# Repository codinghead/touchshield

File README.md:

QTouchShield for Arduino
========================

Introduction to the project
---------------------------

The QTouchShield for Arduino project aims to design a hardware platform for the Arduino MEGA that supports up to 32 configurable capacitive touch inputs.

The inputs can be configured as:

* Buttons
* Sliders
* Wheels
* Proximity sensors

Additionally the project includes the necessary firmware required by the shield's microcontroller to enable this functionality.

Key Capabilties
---------------
* Support up to 32 capacitive touch inputs supporting:
	* up to 8 sliders/wheels
	* up to 32 buttons
	* up to 32 proximity sensors
* Configuration via SPI or UART (RX/TX) interfaces
* Arduino library to simplify integration into sketches

Licensing
---------

The hardware is licensed under the Creative Commons ShareAlike license:

> This work is licensed under the Creative Commons Attribution-ShareAlike 3.0 Unported License.
> To view a copy of this license, visit [http://creativecommons.org/licenses/by-sa/3.0/] (http://creativecommons.org/licenses/by-sa/3.0/) or send
> a letter to:
> Creative Commons, 444 Castro Street, Suite 900, Mountain View, California, 94041, USA.

The software for the project is yet to be developed.

Project Page
------------

For all current information, visit the project page at [codinghead.github.com/touchshield] (http://codinghead.github.com/touchshield/).

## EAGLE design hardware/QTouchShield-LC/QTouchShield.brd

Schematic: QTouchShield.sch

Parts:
C1: 10uF/35V; PANASONIC_C
C33, C40, C43, C45, C47, C49, C51: 100nF; 0805
C34, C41, C44, C46, C48, C50, C52: 33nF; 0805
C35, C38: 2.2uF; 1210
C36, C37: 470pF; 0805
C39, C42: 4.7uF; 1210
IC1: AT32UC3C0512CJEDEC-MS-026; LQFP144
J1: SENSOR 00...07; 2X8-V-MALE-SMT-HARWIN
J2: SENSOR 08...15; 2X8-V-MALE-SMT-HARWIN
J3: SENSOR 16...23; 2X8-V-MALE-SMT-HARWIN
J4: SENSOR 24...31; 2X8-V-MALE-SMT-HARWIN
J5: RES 00...07; 2X8-V-FEMALE-SMT-HARWIN
J6: RES 08...15; 2X8-V-FEMALE-SMT-HARWIN
J7: RES 16...23; 2X8-V-FEMALE-SMT-HARWIN
J8: RES 24...31; 2X8-V-FEMALE-SMT-HARWIN
J9: CAP 00...07; 2X8-V-FEMALE-SMT-HARWIN
J10: CAP 08...15; 2X8-V-FEMALE-SMT-HARWIN
J11: CAP 16...23; 2X8-V-FEMALE-SMT-HARWIN
J12: CAP 24...31; 2X8-V-FEMALE-SMT-HARWIN
J13: SPI-MEGA; 2X4-V-MALE-SMT-HARWIN
J14: SPI-UNO; 2X4-V-MALE-SMT-HARWIN
J15: COMMS Select; 2X8-V-MALE-SMT-HARWIN
J16: DETECT00...15; 2X8-V-MALE-SMT-HARWIN
J17: DETECT16...31; 2X8-V-MALE-SMT-HARWIN
J18: JTAG; 2X5-V-MALE-SMT-HARWIN
J19: TOUCH DATA; 2X5-V-MALE-SMT-HARWIN
JP1: COMMS_SELECT; 1X03
LED1: Yellow; LED-1206
LED2: Green; LED-1206
Q1, Q2, Q3, Q4, Q5, Q6: BSS138; SOT23-3
R1, R2: 39R; 0805
R33, R34: 470Ohm; 0805
R35: 10K; 0805
S1: RESET; TACTILE_SWITCH_SMD
SJ5: RESET-LINK; SJ
U1: ARDUINO-2560-MEGA-R3-SMD; ARDUINO-2560-R3-SMD
X1: Firmware Upgrade Port; PN87520

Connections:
ADCVREFN: C51.1, C52.1, IC1.35 (ADCVREFN)
ADCVREFP: C51.2, C52.2, IC1.34 (ADCVREFP)
ADT-SPI0-MISO: J13.2, J14.2, Q3.2 (S)
ADT-SPI0-MOSI: J13.4, J14.4, Q4.2 (S)
ADT-SPI0-SCK: J13.6, J14.6, Q2.2 (S)
ADT-SPI0-SS: J13.8, J14.8, Q1.2 (S)
ADT-USART0-RXD: J15.4, J15.8, J15.12, J15.16, Q5.2 (S)
ADT-USART0-TXD: J15.2, J15.6, J15.10, J15.14, Q6.2 (S)
ARDUINO_RESET: SJ5.1, U1.RESET
GND: C1.-, C33.2, C34.2, C35.2, C36.2, C37.2, C38.2, C39.2, C40.2, C41.2, C42.2, C43.2, C44.2, C45.2, C46.2, C47.2, C48.2, C49.2, C50.2, IC1.6 (GNDIO1), IC1.37 (GNDANA), IC1.52 (GNDPLL), IC1.56 (GNDCORE), IC1.76 (GNDIO2), IC1.104 (GNDIO3-1), IC1.119 (GNDIO3-2), J1.2, J1.4, J1.6, J1.8, J1.10, J1.12, J1.14, J1.16, J2.2, J2.4, J2.6, J2.8, J2.10, J2.12, J2.14, J2.16, J3.2, J3.4, J3.6, J3.8, J3.10, J3.12, J3.14, J3.16, J4.2, J4.4, J4.6, J4.8, J4.10, J4.12, J4.14, J4.16, J18.2, J18.10, J19.9, JP1.3, LED1.C, LED2.C, S1.1, S1.2, U1.GND_1, U1.GND_2, X1.4
IOREF: Q1.1 (G), Q2.1 (G), Q3.1 (G), Q4.1 (G), Q5.1 (G), Q6.1 (G), U1.IOREF
JTAG_RESET: IC1.142 (RESET_N), J18.6, R35.2, S1.3, S1.4, SJ5.2
JTAG_TCK: IC1.1 (PA00), J18.1
JTAG_TDI: IC1.2 (PA01), J18.9
JTAG_TDO: IC1.3 (PA02), J18.3
JTAG_TMS: IC1.4 (PA03), J18.5
MISO-MEGA: J13.1, U1.50
MOSI-MEGA: J13.3, U1.51
unnamed: LED1.A, R33.1
unnamed: J4.15, J8.16
unnamed: J4.13, J8.14
unnamed: J4.11, J8.12
unnamed: J4.9, J8.10
unnamed: J4.7, J8.8
unnamed: J4.5, J8.6
unnamed: J4.3, J8.4
unnamed: J4.1, J8.2
unnamed: J3.15, J7.16
unnamed: J3.13, J7.14
unnamed: J3.11, J7.12
unnamed: J3.9, J7.10
unnamed: J3.7, J7.8
unnamed: J3.5, J7.6
unnamed: J3.3, J7.4
unnamed: J3.1, J7.2
unnamed: J2.15, J6.16
unnamed: J2.13, J6.14
unnamed: J2.11, J6.12
unnamed: J2.9, J6.10
unnamed: J2.7, J6.8
unnamed: J2.5, J6.6
unnamed: J2.3, J6.4
unnamed: J2.1, J6.2
unnamed: J1.15, J5.16
unnamed: J1.13, J5.14
unnamed: J1.11, J5.12
unnamed: J1.9, J5.10
unnamed: J1.7, J5.8
unnamed: J1.5, J5.6
unnamed: J1.3, J5.4
unnamed: J1.1, J5.2
unnamed: R1.2, X1.2
unnamed: R2.2, X1.3
unnamed: LED2.A, R34.1
QT-DETECT-GENERAL: IC1.21 (PA04), R33.2
RX0: J15.3, U1.RX_PWM00 (0(RX0))
RX1: J15.15, U1.RX1_19 (19(RX1))
RX2: J15.11, U1.RX2_17 (17(RX2))
RX3: J15.7, U1.RX3_15 (15(RX3))
SCK-MEGA: J13.5, U1.52
SDT-SPI0-MISO: IC1.112 (PD05), Q3.3 (D)
SDT-SPI0-MOSI: IC1.111 (PD04), Q4.3 (D)
SDT-SPI0-SCK: IC1.113 (PD06), Q2.3 (D)
SDT-SPI0-SS: IC1.110 (PD03), Q1.3 (D)
SDT-USART0-RXD: IC1.108 (PD01), Q6.3 (D)
SDT-USART0-TXD: IC1.107 (PD00), Q5.3 (D)
SHIELD-DATA-TRANSFER-COM-SELECT: IC1.109 (PD02), JP1.2
SHIELD-DATA-TRANSFER-VISUAL-OUTPUT: IC1.22 (PA05), R34.2
SHIELD-DETECT0: IC1.23 (PA06), J16.1
SHIELD-DETECT1: IC1.24 (PA07), J16.2
SHIELD-DETECT2: IC1.25 (PA08), J16.3
SHIELD-DETECT3: IC1.26 (PA09), J16.4
SHIELD-DETECT4: IC1.27 (PA10), J16.5
SHIELD-DETECT5: IC1.28 (PA11), J16.6
SHIELD-DETECT6: IC1.29 (PA12), J16.7
SHIELD-DETECT7: IC1.30 (PA13), J16.8
SHIELD-DETECT8: IC1.31 (PA14), J16.9
SHIELD-DETECT9: IC1.32 (PA15), J16.10
SHIELD-DETECT10: IC1.33 (PA16), J16.11
SHIELD-DETECT11: IC1.36 (PA19), J16.12
SHIELD-DETECT12: IC1.39 (PA20), J16.13
SHIELD-DETECT13: IC1.40 (PA21), J16.14
SHIELD-DETECT14: IC1.41 (PA22), J16.15
SHIELD-DETECT15: IC1.42 (PA23), J16.16
SHIELD-DETECT16: IC1.43 (PA24), J17.15
SHIELD-DETECT17: IC1.44 (PA25), J17.16
SHIELD-DETECT18: IC1.45 (PA26), J17.13
SHIELD-DETECT19: IC1.46 (PA27), J17.14
SHIELD-DETECT20: IC1.47 (PA28), J17.11
SHIELD-DETECT21: IC1.48 (PA29), J17.12
SHIELD-DETECT22: IC1.120 (PD11), J17.9
SHIELD-DETECT23: IC1.121 (PD12), J17.10
SHIELD-DETECT24: IC1.122 (PD13), J17.7
SHIELD-DETECT25: IC1.123 (PD14), J17.8
SHIELD-DETECT26: IC1.124 (PD15), J17.5
SHIELD-DETECT27: IC1.125 (PD16), J17.6
SHIELD-DETECT28: IC1.126 (PD17), J17.3
SHIELD-DETECT29: IC1.127 (PD18), J17.4
SHIELD-DETECT30: IC1.128 (PD19), J17.1
SHIELD-DETECT31: IC1.129 (PD20), J17.2
SNS0: IC1.140 (PB00), J9.1
SNS1: IC1.141 (PB01), J9.3
SNS2: IC1.143 (PB02), J9.5
SNS3: IC1.144 (PB03), J9.7
SNS4: IC1.7 (PB04), J9.9
SNS5: IC1.8 (PB05), J9.11
SNS6: IC1.9 (PB06), J9.13
SNS7: IC1.10 (PB07), J9.15
SNS8: IC1.11 (PB08), J10.1
SNS9: IC1.12 (PB09), J10.3
SNS10: IC1.13 (PB10), J10.5
SNS11: IC1.14 (PB11), J10.7
SNS12: IC1.15 (PB12), J10.9
SNS13: IC1.16 (PB13), J10.11
SNS14: IC1.17 (PB14), J10.13
SNS15: IC1.18 (PB15), J10.15
SNS16: IC1.19 (PB16), J11.1
SNS17: IC1.20 (PB17), J11.3
SNS18: IC1.57 (PB18), J11.5
SNS19: IC1.58 (PB19), J11.7
SNS20: IC1.59 (PB20), J11.9
SNS21: IC1.60 (PB21), J11.11
SNS22: IC1.61 (PB22), J11.13
SNS23: IC1.62 (PB23), J11.15
SNS24: IC1.63 (PB24), J12.1
SNS25: IC1.64 (PB25), J12.3
SNS26: IC1.65 (PB26), J12.5
SNS27: IC1.66 (PB27), J12.7
SNS28: IC1.67 (PB28), J12.9
SNS29: IC1.68 (PB29), J12.11
SNS30: IC1.69 (PB30), J12.13
SNS31: IC1.70 (PB31), J12.15
SNSK0: IC1.71 (PC00), J5.1, J9.2
SNSK1: IC1.72 (PC01), J5.3, J9.4
SNSK2: IC1.73 (PC02), J5.5, J9.6
SNSK3: IC1.74 (PC03), J5.7, J9.8
SNSK4: IC1.77 (PC04), J5.9, J9.10
SNSK5: IC1.78 (PC05), J5.11, J9.12
SNSK6: IC1.79 (PC06), J5.13, J9.14
SNSK7: IC1.80 (PC07), J5.15, J9.16
SNSK8: IC1.81 (PC08), J6.1, J10.2
SNSK9: IC1.82 (PC09), J6.3, J10.4
SNSK10: IC1.83 (PC10), J6.5, J10.6
SNSK11: IC1.84 (PC11), J6.7, J10.8
SNSK12: IC1.85 (PC12), J6.9, J10.10
SNSK13: IC1.86 (PC13), J6.11, J10.12
SNSK14: IC1.87 (PC14), J6.13, J10.14
SNSK15: IC1.88 (PC15), J6.15, J10.16
SNSK16: IC1.89 (PC16), J7.1, J11.2
SNSK17: IC1.90 (PC17), J7.3, J11.4
SNSK18: IC1.91 (PC18), J7.5, J11.6
SNSK19: IC1.92 (PC19), J7.7, J11.8
SNSK20: IC1.93 (PC20), J7.9, J11.10
SNSK21: IC1.94 (PC21), J7.11, J11.12
SNSK22: IC1.95 (PC22), J7.13, J11.14
SNSK23: IC1.96 (PC23), J7.15, J11.16
SNSK24: IC1.97 (PC24), J8.1, J12.2
SNSK25: IC1.98 (PC25), J8.3, J12.4
SNSK26: IC1.99 (PC26), J8.5, J12.6
SNSK27: IC1.100 (PC27), J8.7, J12.8
SNSK28: IC1.101 (PC28), J8.9, J12.10
SNSK29: IC1.102 (PC29), J8.11, J12.12
SNSK30: IC1.105 (PC30), J8.13, J12.14
SNSK31: IC1.106 (PC31), J8.15, J12.16
SPI-MISO-ALT: J14.1, U1.PWM12 (12)
SPI-MOSI-ALT: J14.3, U1.PWM11 (11)
SPI-SCK-ALT: J14.5, U1.PWM13 (13)
SPI-SS-ALT: J14.7, U1.PWM10 (10)
SS-MEGA: J13.7, U1.53
TOUCH_DATA-MISO: IC1.133 (PD24), J19.7
TOUCH_DATA-MOSI: IC1.132 (PD23), J19.6
TOUCH_DATA-SCK: IC1.131 (PD22), J19.8
TOUCH_DATA-SS: IC1.130 (PD21), J19.5
TX0: J15.1, U1.TX_PWM01 (1(TX0))
TX1: J15.13, U1.TX1_18 (18(TX1))
TX2: J15.9, U1.TX2_16 (16(TX2))
TX3: J15.5, U1.TX3_14 (14(TX3))
USB-DM: IC1.50 (DM), R1.1
USB-DP: IC1.51 (DP), R2.1
VCC: C1.+, C33.1, C34.1, C39.1, C40.1, C41.1, C42.1, C43.1, C44.1, C45.1, C46.1, C47.1, C48.1, C49.1, C50.1, IC1.5 (VDDIO1), IC1.38 (VDDANA), IC1.53 (VDDIN_5), IC1.75 (VDDIO2), IC1.103 (VDDIO3-1), IC1.118 (VDDIO3-2), J18.4, J19.10, JP1.1, R35.1, U1.5V_1, X1.1
VDDCORE: C37.1, C38.1, IC1.55 (VDDCORE)
VDDIN_33: C35.1, C36.1, IC1.54 (VDDIN_33)

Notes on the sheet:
SNSK Lines
JTAG
SNS Lines
Detect Output Bus
SHIELD-DATA-TRANSFER
UART-COMS
Mount close to pins 55 & 56
Keep close to pin 5
Keep close to pin 75
Keep close to pin 103
Keep close to
pin 118
Keep close to pin 53
Keep close to pins 34 & 35
Sensor Headers
Detection
Use jumper pair to
select alternative
UART interface
Select between
SPI and UART
Date: 1st August 2012
Revision: 0.1
Author: Stuart Cording
aka /*CODINGHEAD*/
Designed for use with the
Arduino[TM] MEGA 2560 r3
Project: QTouchShield-LC
Keep close to pins 37 & 38
Decoupling capacitors
Supply decoupling capacitors
R35 not mounted
(Only req. when
Arduino is *not*
Use to link AT32UC3C
RESET_N to
Arduino RESET
Mountain View, California, 94041, USA.
Creative Commons, 444 Castro Street, Suite 900,
http://creativecommons.org/licenses/by-sa/3.0/ or send a letter to:

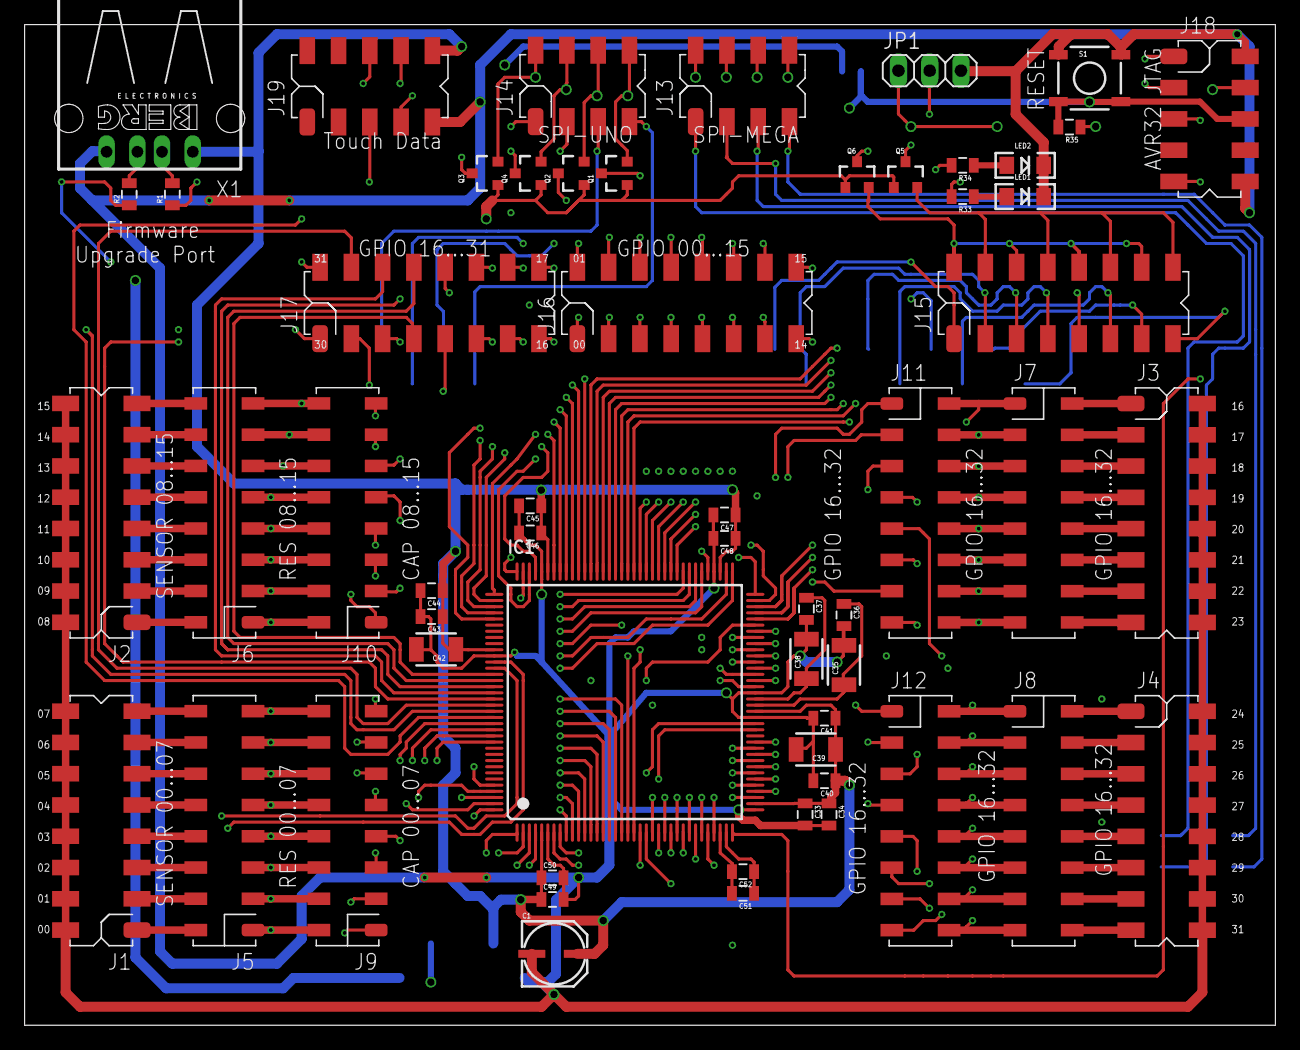
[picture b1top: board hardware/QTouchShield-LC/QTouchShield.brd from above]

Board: 4 copper layers, 101.6 x 81.3 mm, 59 parts (1 on the bottom side), 182 nets.

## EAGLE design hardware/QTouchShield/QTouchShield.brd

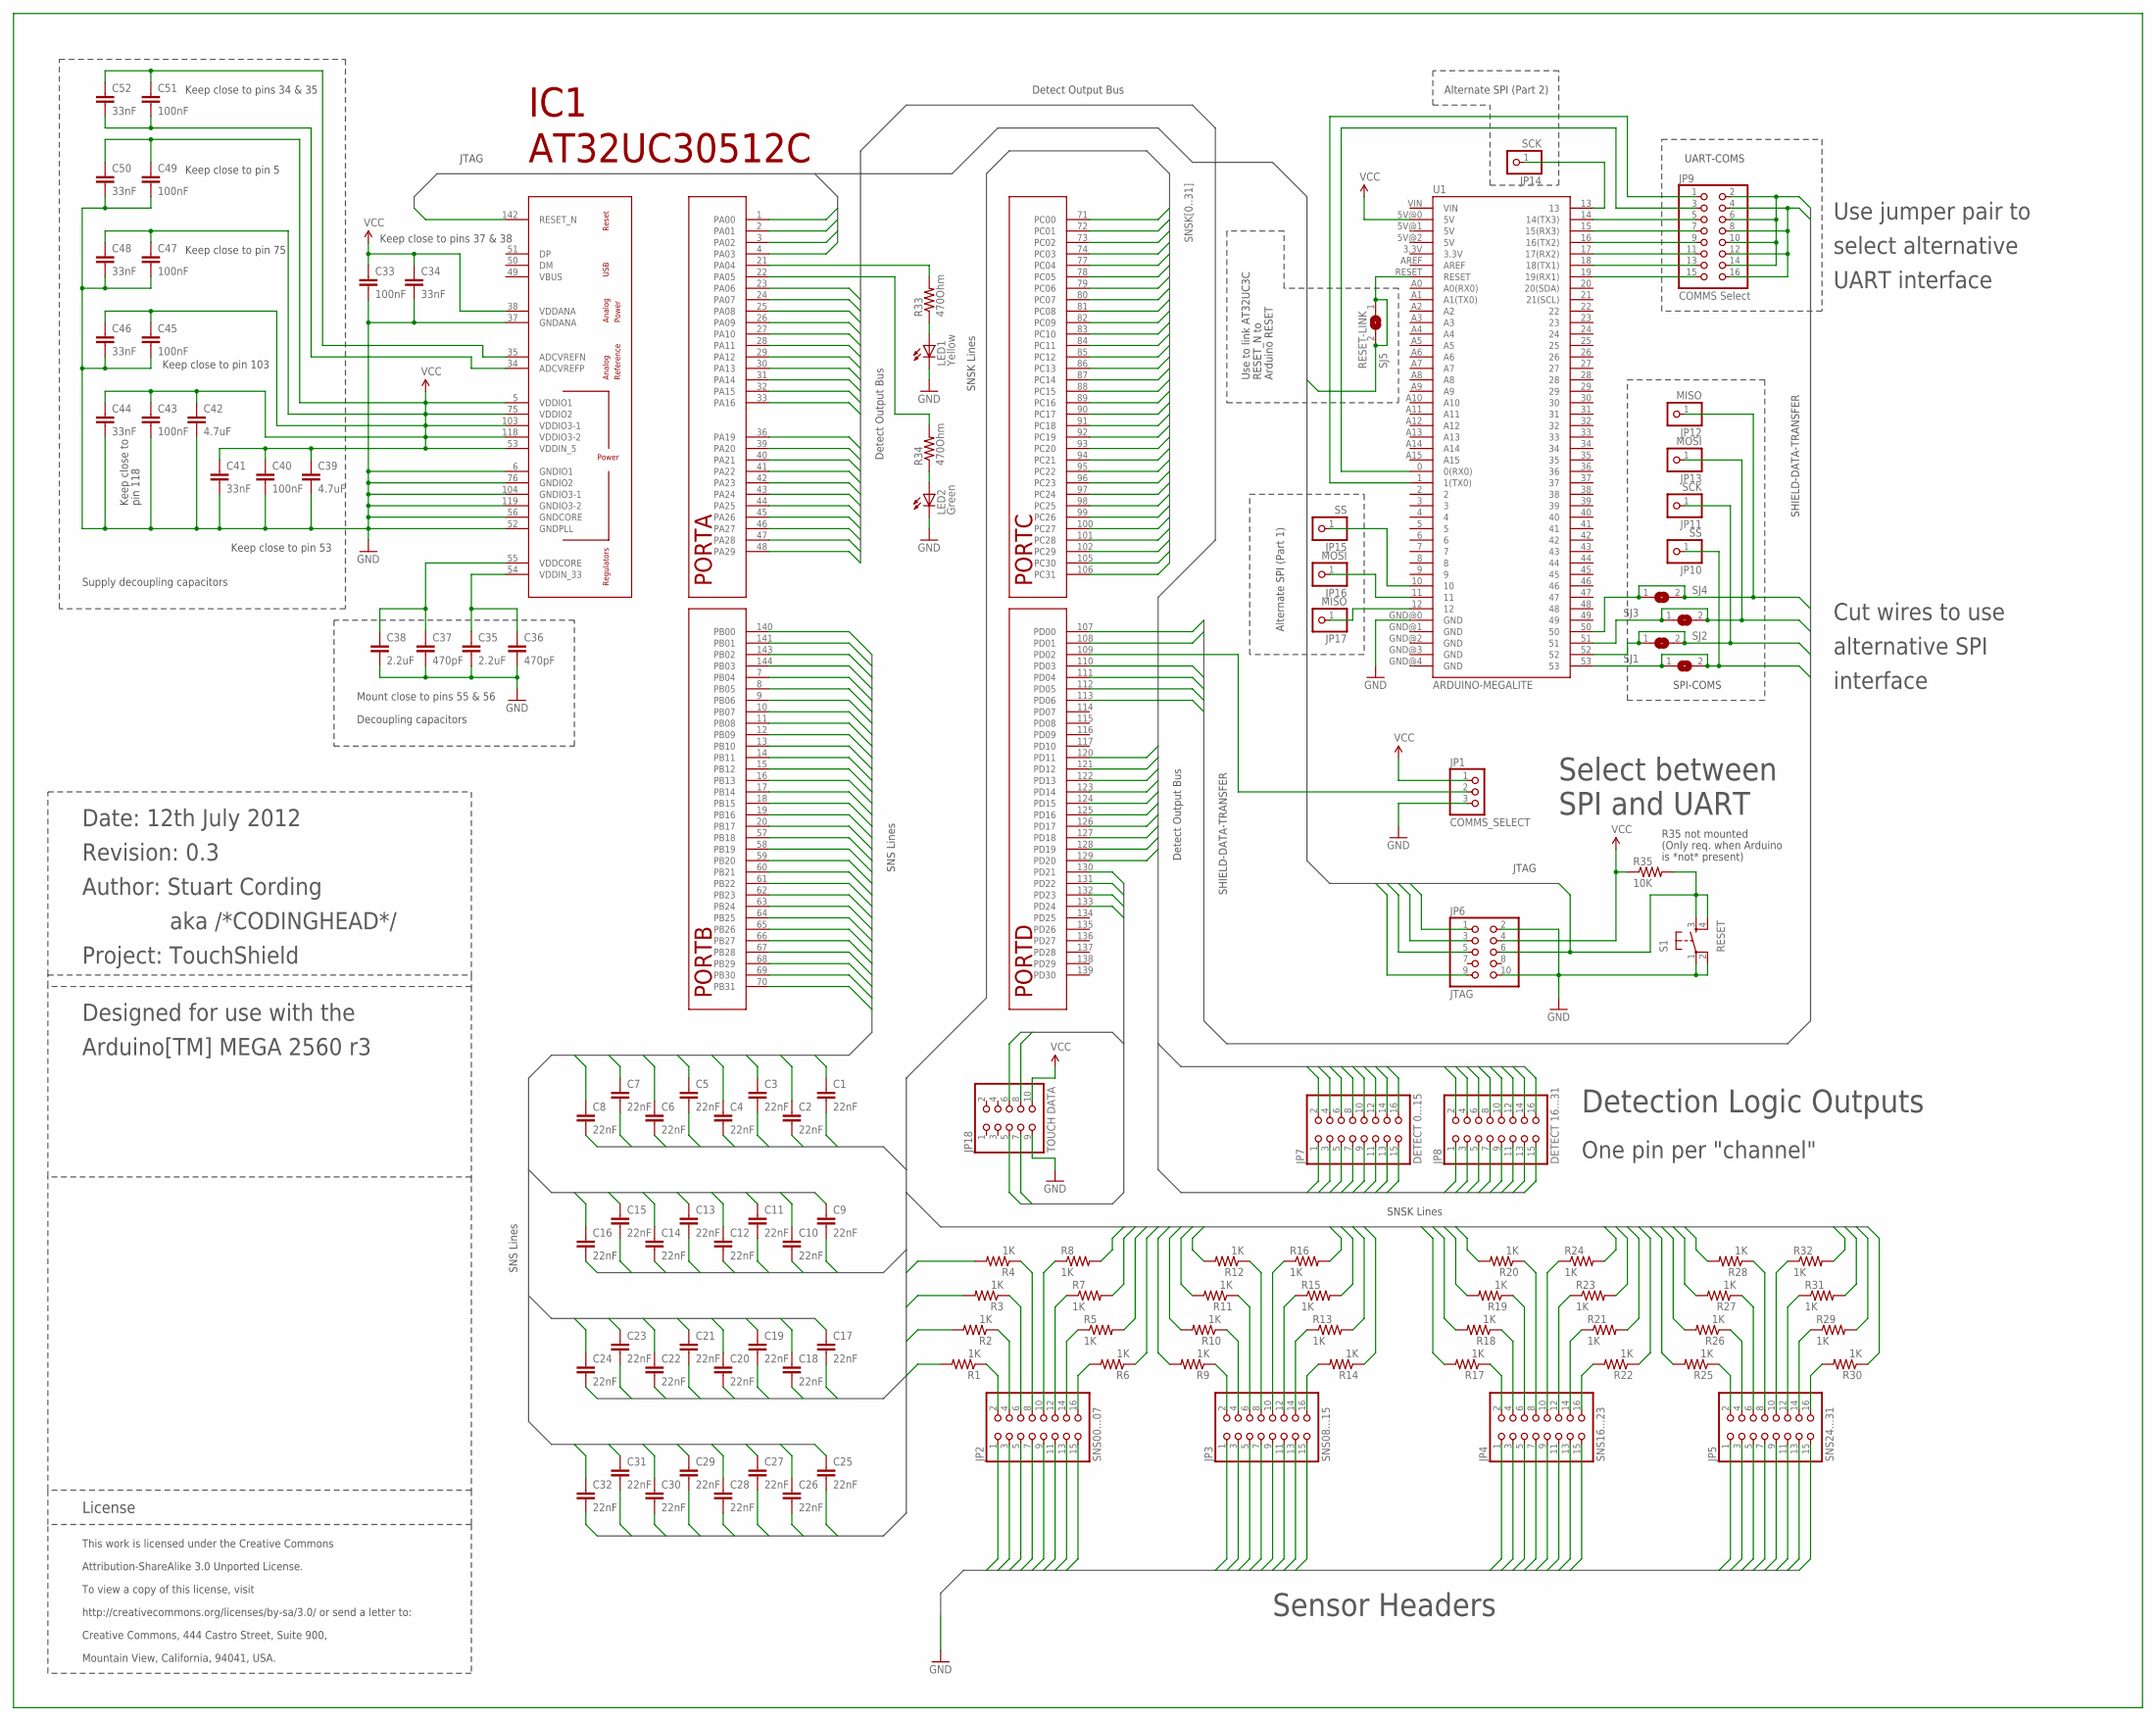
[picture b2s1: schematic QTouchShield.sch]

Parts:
C1, C2, C3, C4, C5, C6, C7, C8, C9, C10, C11, C12, C13, C14, C15, C16, C17, C18, C19, C20, C21, C22, C23, C24, C25, C26, C27, C28, C29, C30, C31, C32: 22nF; 0805
C33, C40, C43, C45, C47, C49, C51: 100nF; 0805
C34, C41, C44, C46, C48, C50, C52: 33nF; 0805
C35, C38: 2.2uF; 1210
C36, C37: 470pF; 0805
C39, C42: 4.7uF; 1210
IC1: AT32UC3C0512CJEDEC-MS-026; LQFP144
JP1: COMMS_SELECT; 1X03
JP2: SNS00...07; 2X08
JP3: SNS08...15; 2X08
JP4: SNS16...23; 2X08
JP5: SNS24...31; 2X08
JP6: JTAG; 2X05
JP7: DETECT 0...15; 2X08
JP8: DETECT 16...31; 2X08
JP9: COMMS Select; 2X08
JP10, JP15: SS; 1X01
JP11, JP14: SCK; 1X01
JP12, JP17: MISO; 1X01
JP13, JP16: MOSI; 1X01
JP18: TOUCH DATA; 2X05
LED1: Yellow; LED-1206
LED2: Green; LED-1206
R1, R2, R3, R4, R5, R6, R7, R8, R9, R10, R11, R12, R13, R14, R15, R16, R17, R18, R19, R20, R21, R22, R23, R24, R25, R26, R27, R28, R29, R30, R31, R32: 1K; 0805
R33, R34: 470Ohm; 0805
R35: 10K; 0805
S1: RESET; TACTILE_SWITCH_SMD
SJ1, SJ2, SJ3, SJ4: SJ
SJ5: RESET-LINK; SJ
U1: ARDUINO-MEGALITE; ARDUINO_MEGA_LITE

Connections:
ADCVREFN: C51.1, C52.1, IC1.35 (ADCVREFN)
ADCVREFP: C51.2, C52.2, IC1.34 (ADCVREFP)
GND: C33.2, C34.2, C35.2, C36.2, C37.2, C38.2, C39.2, C40.2, C41.2, C42.2, C43.2, C44.2, C45.2, C46.2, C47.2, C48.2, C49.2, C50.2, IC1.6 (GNDIO1), IC1.37 (GNDANA), IC1.52 (GNDPLL), IC1.56 (GNDCORE), IC1.76 (GNDIO2), IC1.104 (GNDIO3-1), IC1.119 (GNDIO3-2), JP1.3, JP2.1, JP2.3, JP2.5, JP2.7, JP2.9, JP2.11, JP2.13, JP2.15, JP3.1, JP3.3, JP3.5, JP3.7, JP3.9, JP3.11, JP3.13, JP3.15, JP4.1, JP4.3, JP4.5, JP4.7, JP4.9, JP4.11, JP4.13, JP4.15, JP5.1, JP5.3, JP5.5, JP5.7, JP5.9, JP5.11, JP5.13, JP5.15, JP6.2, JP6.10, JP18.9, LED1.C, LED2.C, S1.1, S1.2, U1.GND@0 (GND)
JTAG_RESET: IC1.142 (RESET_N), JP6.6, R35.2, S1.3, S1.4, SJ5.1, SJ5.2, U1.RESET
JTAG_TCK: IC1.1 (PA00), JP6.1
JTAG_TDI: IC1.2 (PA01), JP6.9
JTAG_TDO: IC1.3 (PA02), JP6.3
JTAG_TMS: IC1.4 (PA03), JP6.5
unnamed: LED1.A, R33.1
unnamed: JP2.2, R1.1
unnamed: JP2.4, R2.1
unnamed: JP2.6, R3.1
unnamed: JP2.8, R4.1
unnamed: JP2.10, R8.1
unnamed: JP2.12, R7.1
unnamed: JP2.14, R5.1
unnamed: JP2.16, R6.2
unnamed: JP3.2, R9.1
unnamed: JP3.4, R10.1
unnamed: JP3.6, R11.1
unnamed: JP3.8, R12.1
unnamed: JP3.10, R16.1
unnamed: JP3.12, R15.1
unnamed: JP3.14, R13.1
unnamed: JP3.16, R14.2
unnamed: JP4.2, R17.1
unnamed: JP4.4, R18.1
unnamed: JP4.6, R19.1
unnamed: JP4.8, R20.1
unnamed: JP4.10, R24.1
unnamed: JP4.12, R23.1
unnamed: JP4.14, R21.1
unnamed: JP4.16, R22.2
unnamed: JP5.2, R25.1
unnamed: JP5.4, R26.1
unnamed: JP5.6, R27.1
unnamed: JP5.8, R28.1
unnamed: JP5.10, R32.1
unnamed: JP5.12, R31.1
unnamed: JP5.14, R29.1
unnamed: JP5.16, R30.2
unnamed: LED2.A, R34.1
QT-DETECT-GENERAL: IC1.21 (PA04), R33.2
RX0: JP9.3, U1.0 (0(RX0))
RX1: JP9.15, U1.19 (19(RX1))
RX2: JP9.11, U1.17 (17(RX2))
RX3: JP9.7, U1.15 (15(RX3))
SDT-SPI0-MISO: IC1.112 (PD05), JP12.1, SJ4.1, SJ4.2, U1.50
SDT-SPI0-MOSI: IC1.111 (PD04), JP13.1, SJ3.1, SJ3.2, U1.51
SDT-SPI0-SCK: IC1.113 (PD06), JP11.1, SJ2.1, SJ2.2, U1.52
SDT-SPI0-SS: IC1.110 (PD03), JP10.1, SJ1.1, SJ1.2, U1.53
SDT-USART0-RXD: IC1.108 (PD01), JP9.4, JP9.8, JP9.12, JP9.16
SDT-USART0-TXD: IC1.107 (PD00), JP9.2, JP9.6, JP9.10, JP9.14
SHIELD-DATA-TRANSFER-COM-SELECT: IC1.109 (PD02), JP1.2
SHIELD-DATA-TRANSFER-VISUAL-OUTPUT: IC1.22 (PA05), R34.2
SHIELD-DETECT0: IC1.23 (PA06), JP7.1
SHIELD-DETECT1: IC1.24 (PA07), JP7.2
SHIELD-DETECT2: IC1.25 (PA08), JP7.3
SHIELD-DETECT3: IC1.26 (PA09), JP7.4
SHIELD-DETECT4: IC1.27 (PA10), JP7.5
SHIELD-DETECT5: IC1.28 (PA11), JP7.6
SHIELD-DETECT6: IC1.29 (PA12), JP7.7
SHIELD-DETECT7: IC1.30 (PA13), JP7.8
SHIELD-DETECT8: IC1.31 (PA14), JP7.9
SHIELD-DETECT9: IC1.32 (PA15), JP7.10
SHIELD-DETECT10: IC1.33 (PA16), JP7.11
SHIELD-DETECT11: IC1.36 (PA19), JP7.12
SHIELD-DETECT12: IC1.39 (PA20), JP7.13
SHIELD-DETECT13: IC1.40 (PA21), JP7.14
SHIELD-DETECT14: IC1.41 (PA22), JP7.15
SHIELD-DETECT15: IC1.42 (PA23), JP7.16
SHIELD-DETECT16: IC1.43 (PA24), JP8.1
SHIELD-DETECT17: IC1.44 (PA25), JP8.2
SHIELD-DETECT18: IC1.45 (PA26), JP8.3
SHIELD-DETECT19: IC1.46 (PA27), JP8.4
SHIELD-DETECT20: IC1.47 (PA28), JP8.5
SHIELD-DETECT21: IC1.48 (PA29), JP8.6
SHIELD-DETECT22: IC1.120 (PD11), JP8.7
SHIELD-DETECT23: IC1.121 (PD12), JP8.8
SHIELD-DETECT24: IC1.122 (PD13), JP8.9
SHIELD-DETECT25: IC1.123 (PD14), JP8.10
SHIELD-DETECT26: IC1.124 (PD15), JP8.11
SHIELD-DETECT27: IC1.125 (PD16), JP8.12
SHIELD-DETECT28: IC1.126 (PD17), JP8.13
SHIELD-DETECT29: IC1.127 (PD18), JP8.14
SHIELD-DETECT30: IC1.128 (PD19), JP8.15
SHIELD-DETECT31: IC1.129 (PD20), JP8.16
SNS0: C1.1, IC1.140 (PB00)
SNS1: C2.1, IC1.141 (PB01)
SNS2: C3.1, IC1.143 (PB02)
SNS3: C4.1, IC1.144 (PB03)
SNS4: C5.1, IC1.7 (PB04)
SNS5: C6.1, IC1.8 (PB05)
SNS6: C7.1, IC1.9 (PB06)
SNS7: C8.1, IC1.10 (PB07)
SNS8: C9.1, IC1.11 (PB08)
SNS9: C10.1, IC1.12 (PB09)
SNS10: C11.1, IC1.13 (PB10)
SNS11: C12.1, IC1.14 (PB11)
SNS12: C13.1, IC1.15 (PB12)
SNS13: C14.1, IC1.16 (PB13)
SNS14: C15.1, IC1.17 (PB14)
SNS15: C16.1, IC1.18 (PB15)
SNS16: C17.1, IC1.19 (PB16)
SNS17: C18.1, IC1.20 (PB17)
SNS18: C19.1, IC1.57 (PB18)
SNS19: C20.1, IC1.58 (PB19)
SNS20: C21.1, IC1.59 (PB20)
SNS21: C22.1, IC1.60 (PB21)
SNS22: C23.1, IC1.61 (PB22)
SNS23: C24.1, IC1.62 (PB23)
SNS24: C25.1, IC1.63 (PB24)
SNS25: C26.1, IC1.64 (PB25)
SNS26: C27.1, IC1.65 (PB26)
SNS27: C28.1, IC1.66 (PB27)
SNS28: C29.1, IC1.67 (PB28)
SNS29: C30.1, IC1.68 (PB29)
SNS30: C31.1, IC1.69 (PB30)
SNS31: C32.1, IC1.70 (PB31)
SNSK0: C1.2, IC1.71 (PC00), R1.2
SNSK1: C2.2, IC1.72 (PC01), R2.2
SNSK2: C3.2, IC1.73 (PC02), R3.2
SNSK3: C4.2, IC1.74 (PC03), R4.2
SNSK4: C5.2, IC1.77 (PC04), R8.2
SNSK5: C6.2, IC1.78 (PC05), R7.2
SNSK6: C7.2, IC1.79 (PC06), R5.2
SNSK7: C8.2, IC1.80 (PC07), R6.1
SNSK8: C9.2, IC1.81 (PC08), R9.2
SNSK9: C10.2, IC1.82 (PC09), R10.2
SNSK10: C11.2, IC1.83 (PC10), R11.2
SNSK11: C12.2, IC1.84 (PC11), R12.2
SNSK12: C13.2, IC1.85 (PC12), R16.2
SNSK13: C14.2, IC1.86 (PC13), R15.2
SNSK14: C15.2, IC1.87 (PC14), R13.2
SNSK15: C16.2, IC1.88 (PC15), R14.1
SNSK16: C17.2, IC1.89 (PC16), R17.2
SNSK17: C18.2, IC1.90 (PC17), R18.2
SNSK18: C19.2, IC1.91 (PC18), R19.2
SNSK19: C20.2, IC1.92 (PC19), R20.2
SNSK20: C21.2, IC1.93 (PC20), R24.2
SNSK21: C22.2, IC1.94 (PC21), R23.2
SNSK22: C23.2, IC1.95 (PC22), R21.2
SNSK23: C24.2, IC1.96 (PC23), R22.1
SNSK24: C25.2, IC1.97 (PC24), R25.2
SNSK25: C26.2, IC1.98 (PC25), R26.2
SNSK26: C27.2, IC1.99 (PC26), R27.2
SNSK27: C28.2, IC1.100 (PC27), R28.2
SNSK28: C29.2, IC1.101 (PC28), R32.2
SNSK29: C30.2, IC1.102 (PC29), R31.2
SNSK30: C31.2, IC1.105 (PC30), R29.2
SNSK31: C32.2, IC1.106 (PC31), R30.1
SPI-MISO-ALT: JP17.1, U1.12
SPI-MOSI-ALT: JP16.1, U1.11
SPI-SCK-ALT: JP14.1, U1.13
SPI-SS-ALT: JP15.1, U1.10
TOUCH_DATA-MISO: IC1.133 (PD24), JP18.7
TOUCH_DATA-MOSI: IC1.132 (PD23), JP18.6
TOUCH_DATA-SCK: IC1.131 (PD22), JP18.8
TOUCH_DATA-SS: IC1.130 (PD21), JP18.5
TX0: JP9.1, U1.1 (1(TX0))
TX1: JP9.13, U1.18 (18(TX1))
TX2: JP9.9, U1.16 (16(TX2))
TX3: JP9.5, U1.14 (14(TX3))
VCC: C33.1, C34.1, C39.1, C40.1, C41.1, C42.1, C43.1, C44.1, C45.1, C46.1, C47.1, C48.1, C49.1, C50.1, IC1.5 (VDDIO1), IC1.38 (VDDANA), IC1.53 (VDDIN_5), IC1.75 (VDDIO2), IC1.103 (VDDIO3-1), IC1.118 (VDDIO3-2), JP1.1, JP6.4, JP18.10, R35.1, U1.5V@0 (5V)
VDDCORE: C37.1, C38.1, IC1.55 (VDDCORE)
VDDIN_33: C35.1, C36.1, IC1.54 (VDDIN_33)

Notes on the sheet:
SNSK Lines
JTAG
SNS Lines
Detect Output Bus
SHIELD-DATA-TRANSFER
UART-COMS
SPI-COMS
Mount close to pins 55 & 56
Keep close to pin 5
Keep close to pin 75
Keep close to pin 103
Keep close to
pin 118
Keep close to pin 53
Keep close to pins 34 & 35
Sensor Headers
Detection Logic Outputs
Cut wires to use
alternative SPI
interface
Use jumper pair to
select alternative
UART interface
Select between
SPI and UART
Date: 12th July 2012
Revision: 0.3
Author: Stuart Cording
aka /*CODINGHEAD*/
Designed for use with the
Arduino[TM] MEGA 2560 r3
Project: TouchShield
Keep close to pins 37 & 38
Decoupling capacitors
Supply decoupling capacitors
Alternate SPI (Part 2)
Alternate SPI (Part 1)
R35 not mounted
(Only req. when Arduino
is *not* present)

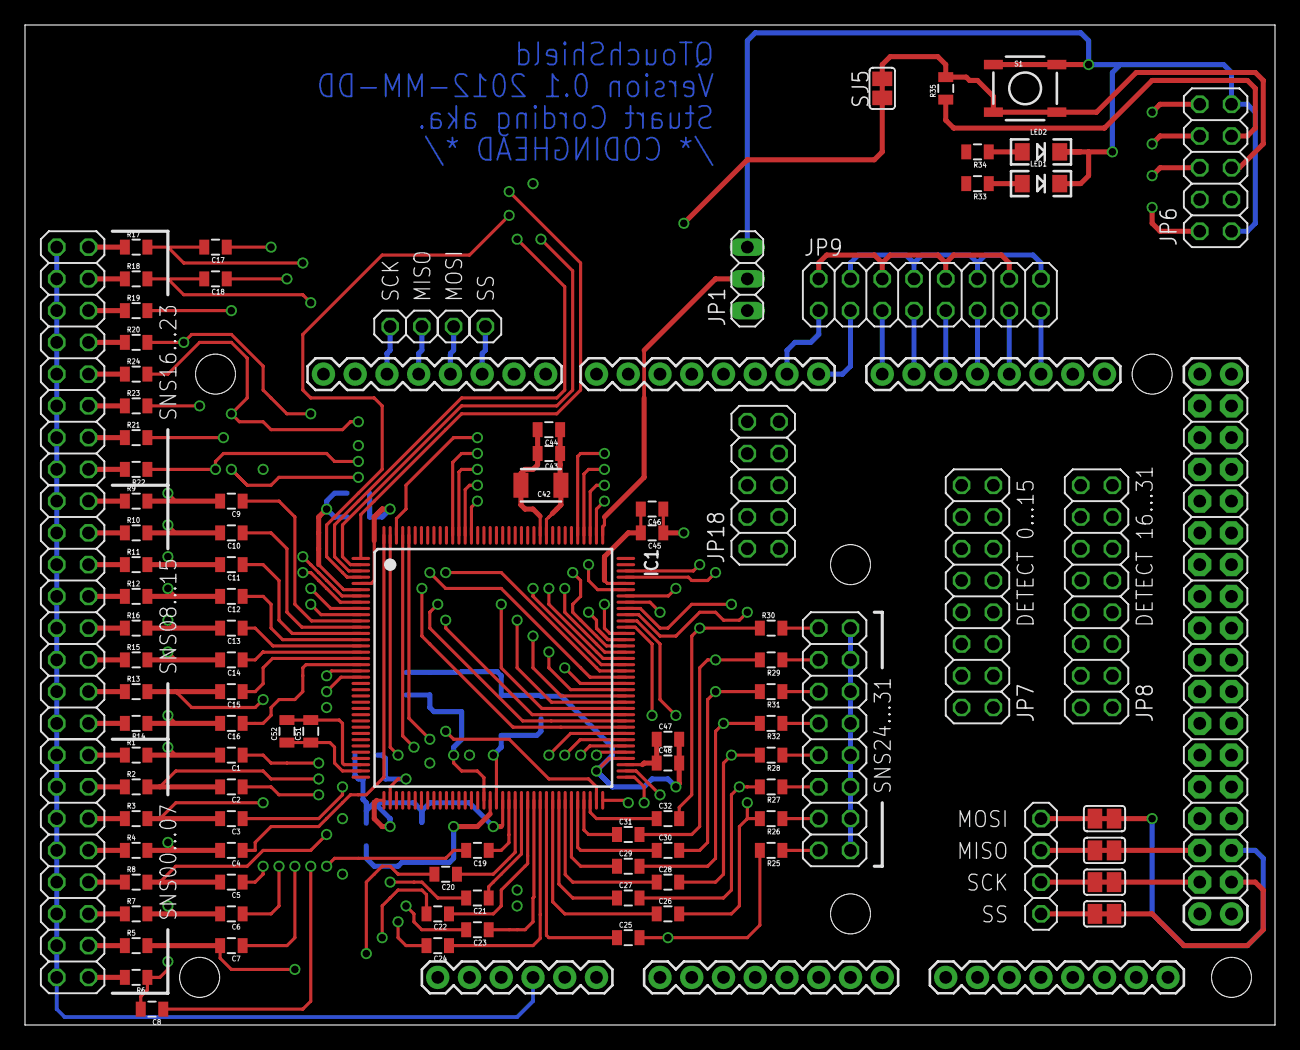
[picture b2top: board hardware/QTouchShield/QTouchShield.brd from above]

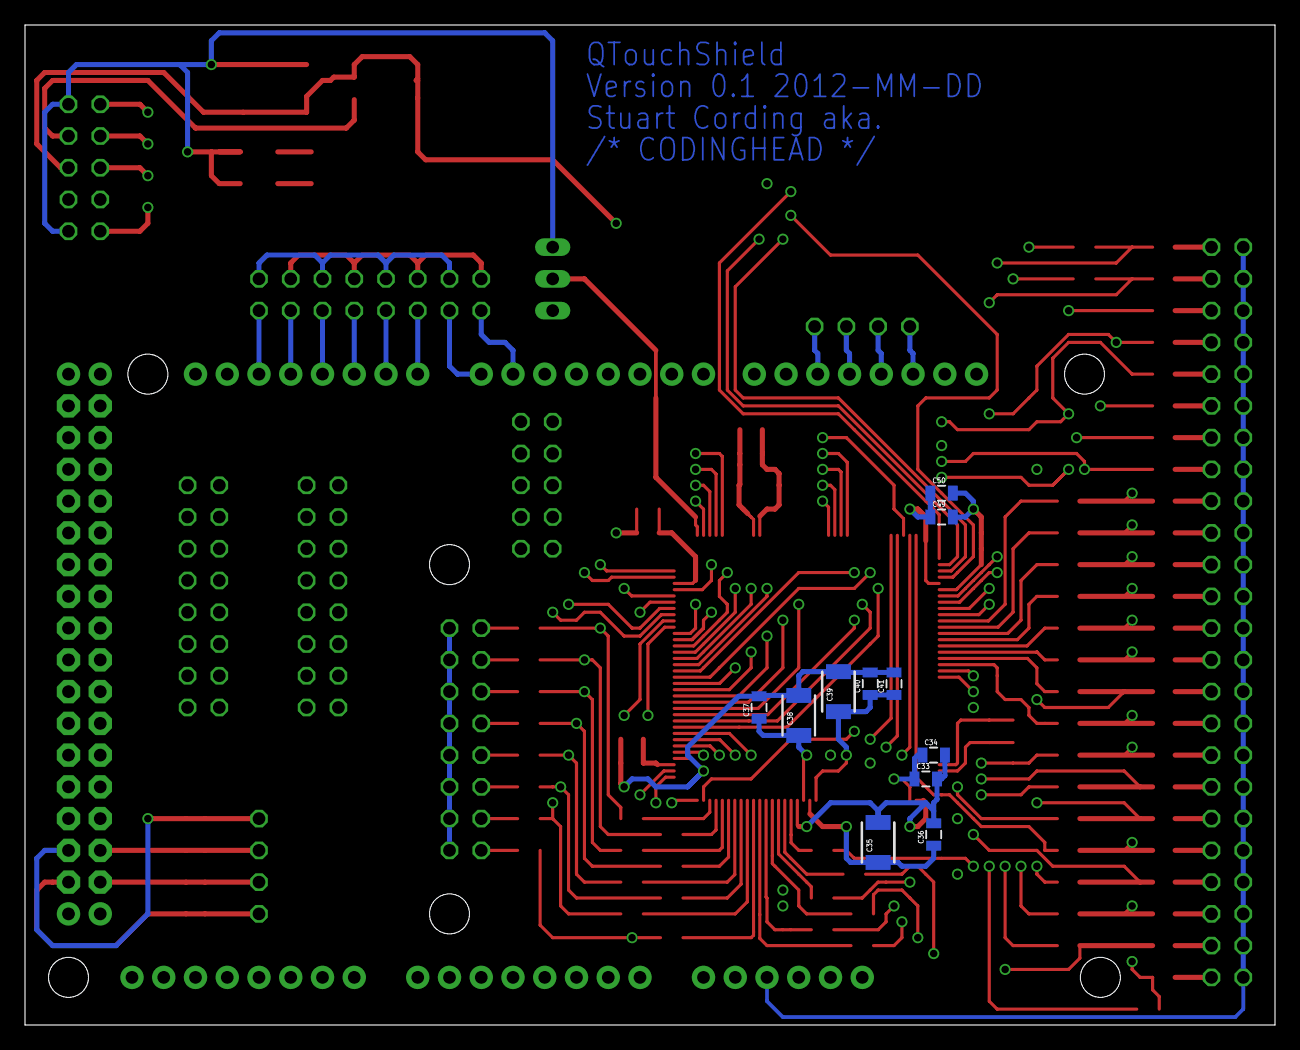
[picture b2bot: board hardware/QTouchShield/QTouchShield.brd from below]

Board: 4 copper layers, 100.0 x 80.0 mm, 115 parts (11 on the bottom side), 166 nets.

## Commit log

2012-07-01 Added project image.
    Added images to be associated with this project.
2012-07-01 Added EagleCAD schematic and board design.
    Schematic and board design (not yet complete) added to repo.
2012-07-01 First GitHub page commit
2012-07-01 Added packaging data for TQFP/LQFP 144 packages.
    Added drawings for the TQFP and LQFP packages. Still unsure as to the
    actual footprint needed for the PCB CAD design.
2012-07-02 Added logos for project.
    Added logos in various formats for this project.
2012-07-02 Changed LQFP-144 footprint.
    Ripped up LQFP-144 package footprint and replaced by footprint from an
    offical EagleCAD library.
2012-07-02 Updated .gitignore; removed unnecessary Eagle CAD files.
    Updated .gitignore to ignore temporary Eagle CAD file.
    Deleted these file from the repo.
2012-07-02 Fixed slash direction in .gitignore
    Slash direction was incorrect in directory paths.
2012-07-02 Rotated AT32UC3C packge to correct position.
    Package was at wrong angle related to the related components. Fixed.
2012-07-02 Updated the README file.
    Added more detailed content regarding the project's aims to the
    README file.
2012-07-02 Fixed README error with bullets.
    README file bullets incorrectly indented - fixed.
2012-07-02 Another attempt at bullet indenting of REAME.md
2012-07-02 Removed random directories and files.
    Somehow various directories and files ended up in the gh-pages branch.
    Removed.
2012-07-02 First pass at project HTML home page.
2012-07-02 Added project logo.
    Porject logo added to the project page branch.
2012-07-02 First realistic overview of project.
    HTML project page with first real details of project.
2012-07-02 Fixed text formatting for some headings.
2012-07-09 Added Creative Commons Share Alike license logos
2012-07-09 Added Creative Commons logo to schematic
    Imported Creative Commons Share Alike logo into the schematic.
2012-07-10 Updated Eagle project file.
2012-07-10 Added hardware licensing info to README
    Added the create commons ShareAlike license to README.
2012-07-10 Fixed typo in README
2012-07-10 Added blockquote around license reference.
2012-07-11 Move hardware to 4-layer board.
    32-Touch channels in a reasonable board space was not working out. Moved
    to 4-layer board.
2012-07-11 Added pin assignment table to project.
    Pin assignment table added. Links ARV32 pins to Arduino MEGA board layout
    plus defines other board signalling.
2012-07-12 Further routing added on SNS and SNSK lines.
2012-07-12 Added cuttable bridges for RESET and SPI.
    Added cuttable PCB bridges that allow default:
    - RESET switch of shield connected to RESET of Arduino
    - SPI interface selected as default interface
    Defaults can be changed by cutting the bridges through with a scalpel.
2012-07-12 Added license text to schematic.
2012-07-12 Added project logo to schematic.
2012-07-12 Touched design - no major changes
2012-07-12 Added 3D pictures of board.
    3D images from SketchUp and Maxwell rendered version too!
2012-07-12 Added SketchUp and EagleUp files.
2012-07-13 Updated Google SketchUp image with latest 3D models /*******************************************************************************
2012-07-13 Listed new LED models and Capacitor models for import.
    Added new models to list for SketchUp/EagleUp.
2012-07-13 Updated images of 3D and 2D PCB drawings
2012-07-13 Added new image for web page.
    Added images of 2D and 3D rendered PCB for project web page.
2012-07-13 Added update to hardware description.
    Added hardware description, licensing update and images of board from
    SketchUp/EagleUp/Maxwell.
2012-07-13 Saved SketchUp with latest component additions.
2012-07-13 Updated date of last edit - was incorrect.
2012-07-13 Update .gitignore
    Added rules to ignore build files created during EagleUp file
    generation and SketchUp backup files.
2012-07-27 Fixed error with the SPI MOSI/MISO connections.
    The MOSI/MISO connections were the wrong way round.
    Added the relationship between the UC3C MCU and the "Port Pins" on the
    STK600.
2012-07-27 Ignored Microsoft Excel temporary files.
2012-07-27 Added first test code for Arduino MEGA running SPI interface.
    Small sketch to output some data on the SPI interface as MASTER.
    Blinks LED on Pin13 after every transfer. Used to confirm that
    UC3C is working correctly as slave.
2012-07-27 Swapped MISO/MOSI connection to Arduino - wrong way round.
    The MISO/MOSI lines from the UC3C to the Arduino were swapped.
    Fixed in the schematic and board.
2012-07-27 Got SPI Master mode on Arduino to loop-back data with UC3C.
    Changes made allow loop-back with UC3C on STK600.
2012-07-27 Started progress report to help track open issues.
    Progress report helps to track open issues and make notes on any
    info noticed during development.
2012-07-27 Added UC3C0512C test project performing SPI slave loop-back.
    First commit of UC3C0512C SPI slace loop-back code.
2012-07-27 Updated gitignore to ignore Atmel Studio files.
    Ignored Atmel Studio generated files and related compiler files.
2012-07-27 Added last missing file from UC3C SPI loop-back project.
2012-07-30 Added project progress tracker.
    Created basic tracker to kep note of progress and plan next steps.
2012-07-30 Update to first Arduino SPI transfer test code.
    Functional test code for Arduino MEGA to send and receive
    data from slave SPI device. SS pin held low continuously.
2012-07-30 Added 5-byte SPI transfer test for arduino
    SPI Master to slave transfer test where 5 bytes are transferred
    in one SS pin low phase.
2012-07-30 Added new ASF drivers to UC3C application.
    Added SCIF, PM and FLASHC driver from ASF to UC3C test project.
2012-07-30 Added initialisation of the oscillator and clock tree for UC3C.
    Initialised the clock to use internal 120MHz clock. This helps to ensure
    that the SPI in slave mode can handle the master's data transfer rates.
2012-07-30 Added updated Atmel Studio project files.
    Added files updated by Atmel Studio after adding more ASF drivers.
2012-07-30 Updated Arduino 5-byte SPI transfer test for maximum transfer speed.
    Test updated to run at ATmega's maximum SPI data speed and no waits
    during the transfer or post/prior to changing the SS slave select line.
    LED is now only turned on if data transfer fails. Otherwise it remains
    off.
2012-07-30 Update to progress tracker - re: SPI MASTER/SLAVE progress.
2012-07-30 Screen shots from logic-analyser taken during SPI testing
    Various screen shots taken during testing of SPI transfers.
2012-07-30 Finalised version of project with functional SPI slave.
    Finalised version of test code for SPI slave with correct settings for
    internal clocks etc.
    Will be used as basis for other tests prior to full application
    development.
2012-07-30 Added firmware flow diagram to spreadsheet.
    Started rough firmware flow diagram for the code. Added it here to
    be with the pin assignments etc.
2012-07-30 Modified naming of detect pins as being "per sensor".
    In keeping with the whole QTouch library, the detect pins are now
    named as being "per sensor", since a slider or rotor takes up 3
    channels which make up 1 sensor.
2012-07-30 Updated progress tracking spreadsheet.
2012-07-30 Added comment regarding detect pins on schematic.
    Noted that detect pins output "channel" detections, not "sensor"
    detections, as defined in the QTouch library.
2012-07-31 Added pin definition for QT600 interface board debug interface.
    Added SPI bit bang Data Interface pins for interfacing with the
    QT600 Interface Board to use with QTouch Studio for debugging.
2012-07-31 Added TOUCH DATA header for data transfer to QT600 Interface Board
    TOUCH DATA header added. This is the bit-banged SPI interface for
    transferring debug data to the QT600 board for analysing touch data
    with QTouch Studio.
2012-07-31 Starting adding decoupling capacitors in correct places.
    Decoupling caps being placed near to their associated pins. Not yet
    complete.
2012-08-01 Completed routing of cap sense lines plus JTAG & QT600 Debug IF
2012-08-01 Further board updates and pin changes.
2012-08-02 Added drawings for pin headers and receptacles.
    Added 0.1" pitch SMD header drawings needed for PCB footprints.
2012-08-02 Added new Leaded Component version of QTouch Shield.
    Added new version of shield that allows leaded caps and resistors to be
    fitted between the AVR32 and the capacitive sensors.
    First version of the new board.
2012-08-02 Updated .gitignore
    Updated rules to ignore EagleCAD and Sketchup files in the
    hardware directory.
2012-08-02 Removed global gitignore file.
2012-08-02 Added new .gitignore files handling file in each subdirectory.
    Each subdirectory (hardware, software) now has directory specific
    gitignore files to handle the file types in those directories.
2012-08-03 Added USB Connector (B-Large) for firmware updates.
2012-08-03 Board ripped up - new surface mount headers fitted.
    Ripped-up entire board. Most headers have been changed to surface mount
    type.
2012-08-03 Added new surface mount header datasheet and SketchUp Model.
2012-08-03 Updated progress report.
2012-08-03 Added new HARWIN connector to list
2012-08-03 Added TODO list to Excel file.
2012-08-03 Major update to LC version of shield.
    Major update to shield design including:
    - Moving headers to surface mount technology
    - Including level shifters for SPI and USART i/f
    - USB connector for firmware flash upgrade (not yet complete)
    - Jumper system for selecting MEGA or UNO style SPI interface
    - Plus other tidying up
2012-08-03 Update of SketchUp/EagleUp drawing for new LC board.
2012-08-09 Another attempt, more successful, at routingh the board!
2012-08-09 Updated the Pin Assignment file.
2012-08-09 Added full list of STK600 pins to AVR32 MCU pinning list.
2012-08-09 95% complete routing of board; extra VCC decoupling; USB changes.
    Routing about 95% complete.
    Added extra 10uF cap in the VCC supply.
    Added in-line resistors in the D+/D- lines.
2012-08-09 Update progress on board.
2012-08-09 Split Arduino reset electrically from UC3 & JTAG reset signals.
    Split resets. If user wants to reset Arduino from switch, they have to
    solder blob the jumper by hand.
2012-08-10 Updated project HTML page to match current plan.
2012-08-10 Final routed board for LC version.
    Board finally routed with the LC layout.
    No known major issues to resolve.
    Consider only ground-plane under MCU and review from STROHAL.
2012-08-10 Latest version of 3D model of LV version of board.
2012-08-21 Update of project progess and todo: list
2012-08-21 Updated schematic and board, especially silk screen
2012-08-21 Updated pin assignment documentation related to testing undertaken.
2012-08-21 Added -LC version of board images and Maxwell render for project page.
2012-08-21 Project homepage updated with latest images of -LC board.
    /*******************************************************************************
2012-08-24 Added the BitBangSPI files needed to support Debug interface for QTouch.
2012-09-17 Modified this .gitignore as wildcards were messing things up

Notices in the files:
parts and their libraries:
SparkFun: Licensing: CC v3.0 Share-Alike You are welcome to use this library for commercial purposes.
